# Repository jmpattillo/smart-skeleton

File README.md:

# smart-skeleton

This repository houses all files needed for the Smart Skeleton.  Please see  https://doi.org/10.1152/advan.00145.2019
to learn more about this project.

See update log for latest changes

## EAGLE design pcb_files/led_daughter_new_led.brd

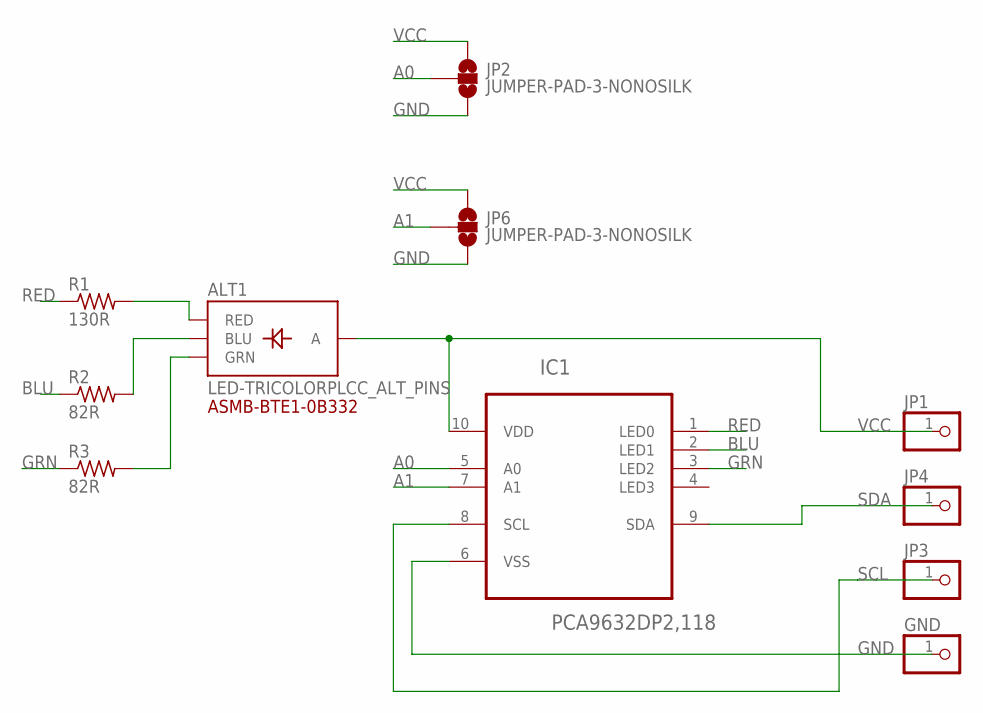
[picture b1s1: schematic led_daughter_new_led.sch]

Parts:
ALT1: LED-TRICOLORPLCC_ALT_PINS; LED-TRICOLOR-PLCC
GND: PINHD-1X1CB; 1X01-CLEANBIG
IC1: PCA9632DP2,118; SOP50P490X110-10N
JP1, JP3, JP4: PINHD-1X1CB; 1X01-CLEANBIG
JP2, JP6: JUMPER-PAD-3-NONOSILK; PAD-JUMPER-3-NO_NO_SILK
R1: 130R; R0603
R2, R3: 82R; R0603

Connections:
A0: IC1.5 (A0), JP2.2
A1: IC1.7 (A1), JP6.2
BLU: IC1.2 (LED1), R2.1
GND: GND.1, IC1.6 (VSS), JP2.3, JP6.3
GRN: IC1.3 (LED2), R3.1
unnamed: ALT1.PAD3 (RED), R1.2
unnamed: ALT1.PAD1 (BLU), R2.2
unnamed: ALT1.PAD4 (GRN), R3.2
RED: IC1.1 (LED0), R1.1
SCL: IC1.8 (SCL), JP3.1
SDA: IC1.9 (SDA), JP4.1
VCC: ALT1.PAD2 (A), IC1.10 (VDD), JP1.1, JP2.1, JP6.1

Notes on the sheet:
ASMB-BTE1-0B332

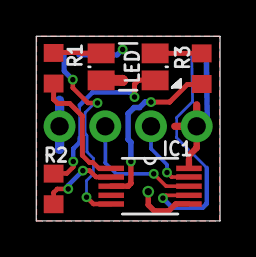
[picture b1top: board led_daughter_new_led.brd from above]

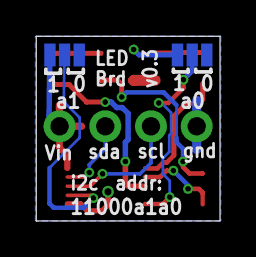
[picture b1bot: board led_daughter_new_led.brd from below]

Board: 2 copper layers, 10.2 x 10.3 mm, 11 parts (2 on the bottom side), 12 nets.

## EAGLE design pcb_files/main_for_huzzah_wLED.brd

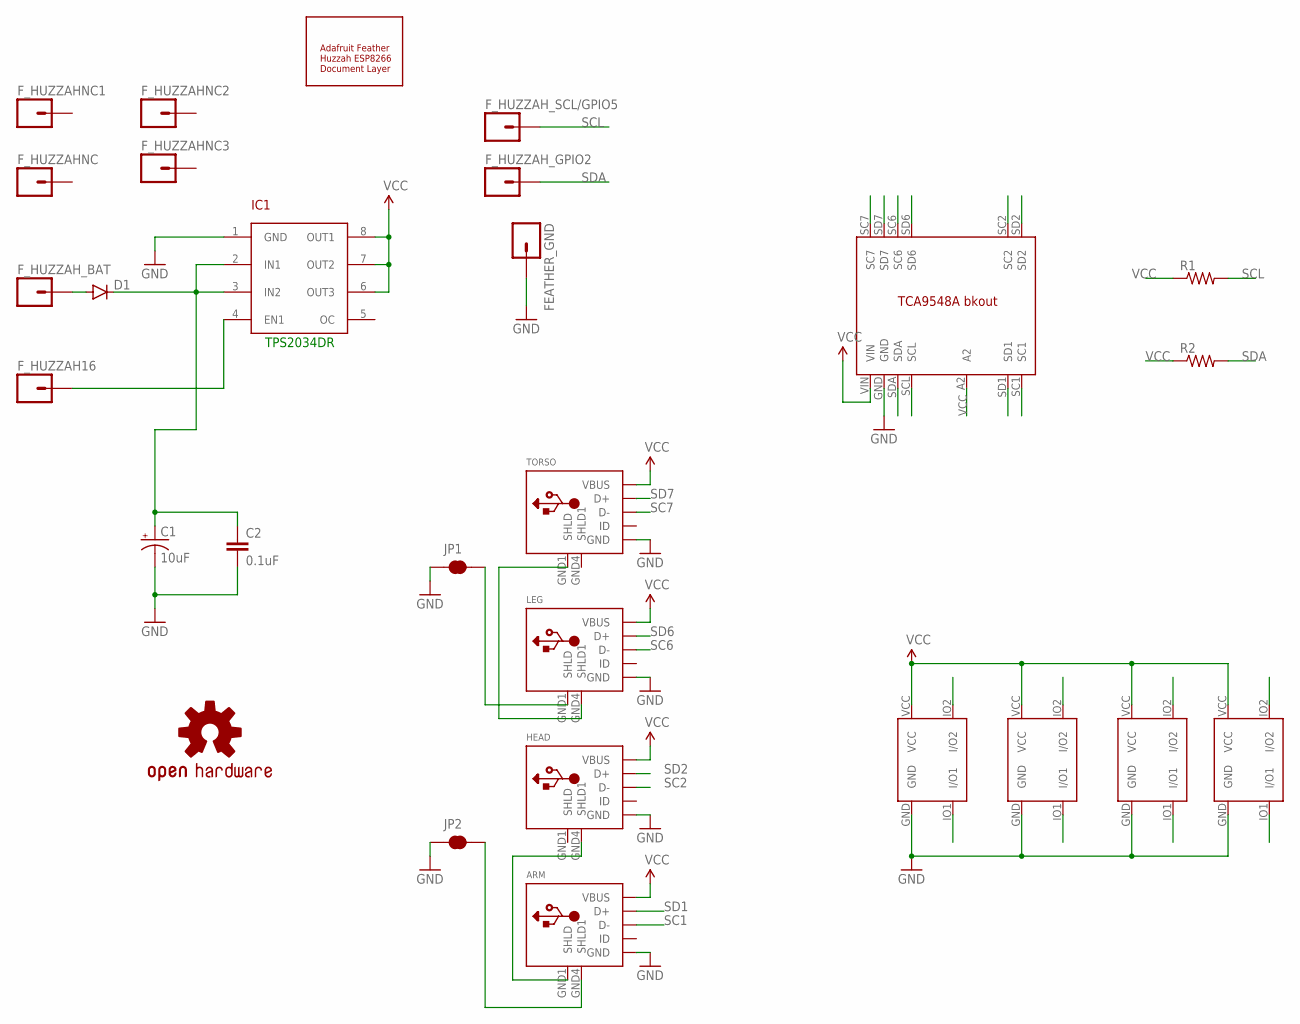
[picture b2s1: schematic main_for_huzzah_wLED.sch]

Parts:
ARM: USB; USB-MINIB-THM-MOLEX_NOSLK
C1: 10uF; CPOL-RADIAL-10UF-25V
C2: 0.1uF; CAP-PTH-SMALL
D1: DIODEKIT2; DIODE-1N4001-KIT
FEATHER_GND: M01; 1X01SMALL_NS
F_HUZZAH16: M01; 1X01SMALL_NS
F_HUZZAHNC, F_HUZZAHNC1, F_HUZZAHNC2, F_HUZZAHNC3: M01; 1X01SMALL_NS
F_HUZZAH_BAT: M01; 1X01SMALL_NS
F_HUZZAH_GPIO2: M01; 1X01SMALL_NS
F_HUZZAH_SCL/GPIO5: M01; 1X01SMALL_NS
HEAD: USB; USB-MINIB-THM-MOLEX_NOSLK
IC1: TPS2055A; SO-08
JP1, JP2: JUMPER-PAD-2-NC_BY_TRACENO_SILK; PAD-JUMPER-2-NC_BY_TRACE_NO_SILK
LEG: USB; USB-MINIB-THM-MOLEX_NOSLK
LOGO1: OSHW-LOGOM; OSHW-LOGO-M
R1, R2: RESISTORAXIAL-0.3; AXIAL-0.3
TORSO: USB; USB-MINIB-THM-MOLEX_NOSLK
U$1: TCA9548_MIN; TCA9548_NOEXTRA
U$2, U$3, U$4, U$5: TVS_ARRAY_CD143A; SOT-143
U$7: FEATHER_HUZZAH_DOCUMENT; FEATHER_HUZZAH_DOC_ONLY

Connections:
GND: ARM.GND, C1.2 (-), C2.2, FEATHER_GND.P$1, HEAD.GND, IC1.1 (GND), JP1.1, JP2.1, LEG.GND, TORSO.GND, U$1.GND, U$2.GND, U$3.GND, U$4.GND, U$5.GND
unnamed: LEG.GND4 (SHLD1), TORSO.GND1 (SHLD)
unnamed: JP1.2, LEG.GND1 (SHLD)
unnamed: ARM.GND1 (SHLD), HEAD.GND4 (SHLD1)
unnamed: ARM.GND4 (SHLD1), JP2.2
unnamed: D1.A, F_HUZZAH_BAT.P$1
unnamed: F_HUZZAH16.P$1, IC1.4 (EN1)
unnamed: C1.1 (+), C2.1, D1.C, IC1.2 (IN1), IC1.3 (IN2)
SC1: ARM.D-, U$1.SC1, U$3.IO1 (I/O1)
SC2: HEAD.D-, U$1.SC2, U$2.IO1 (I/O1)
SC6: LEG.D-, U$1.SC6, U$5.IO1 (I/O1)
SC7: TORSO.D-, U$1.SC7, U$4.IO1 (I/O1)
SCL: F_HUZZAH_SCL/GPIO5.P$1, R1.P$2 (2), U$1.SCL
SD1: ARM.D+, U$1.SD1, U$3.IO2 (I/O2)
SD2: HEAD.D+, U$1.SD2, U$2.IO2 (I/O2)
SD6: LEG.D+, U$1.SD6, U$5.IO2 (I/O2)
SD7: TORSO.D+, U$1.SD7, U$4.IO2 (I/O2)
SDA: F_HUZZAH_GPIO2.P$1, R2.P$2 (2), U$1.SDA
VCC: ARM.VBUS, HEAD.VBUS, IC1.6 (OUT3), IC1.7 (OUT2), IC1.8 (OUT1), LEG.VBUS, R1.P$1 (1), R2.P$1 (1), TORSO.VBUS, U$1.A2, U$1.VIN, U$2.VCC, U$3.VCC, U$4.VCC, U$5.VCC

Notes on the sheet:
TPS2034DR

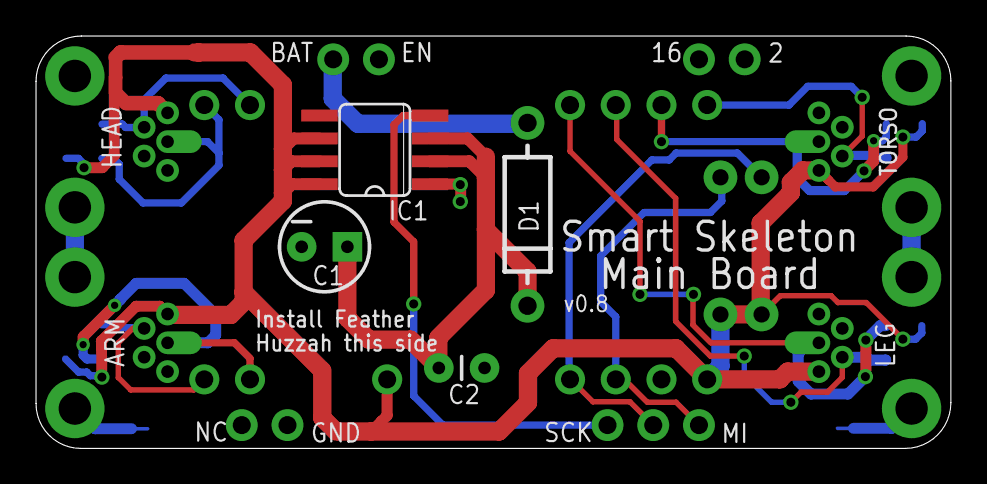
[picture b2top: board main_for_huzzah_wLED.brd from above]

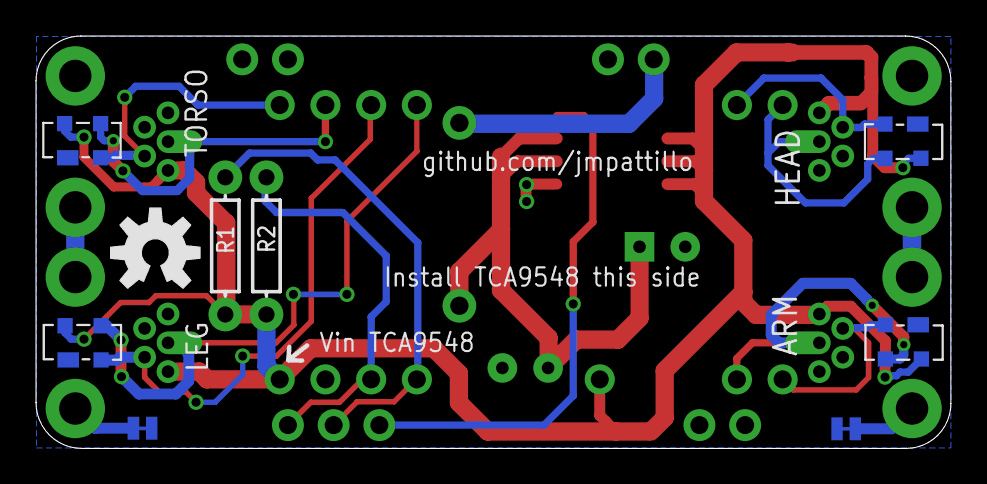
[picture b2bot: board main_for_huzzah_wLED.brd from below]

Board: 2 copper layers, 50.8 x 22.9 mm, 28 parts (10 on the bottom side), 19 nets.

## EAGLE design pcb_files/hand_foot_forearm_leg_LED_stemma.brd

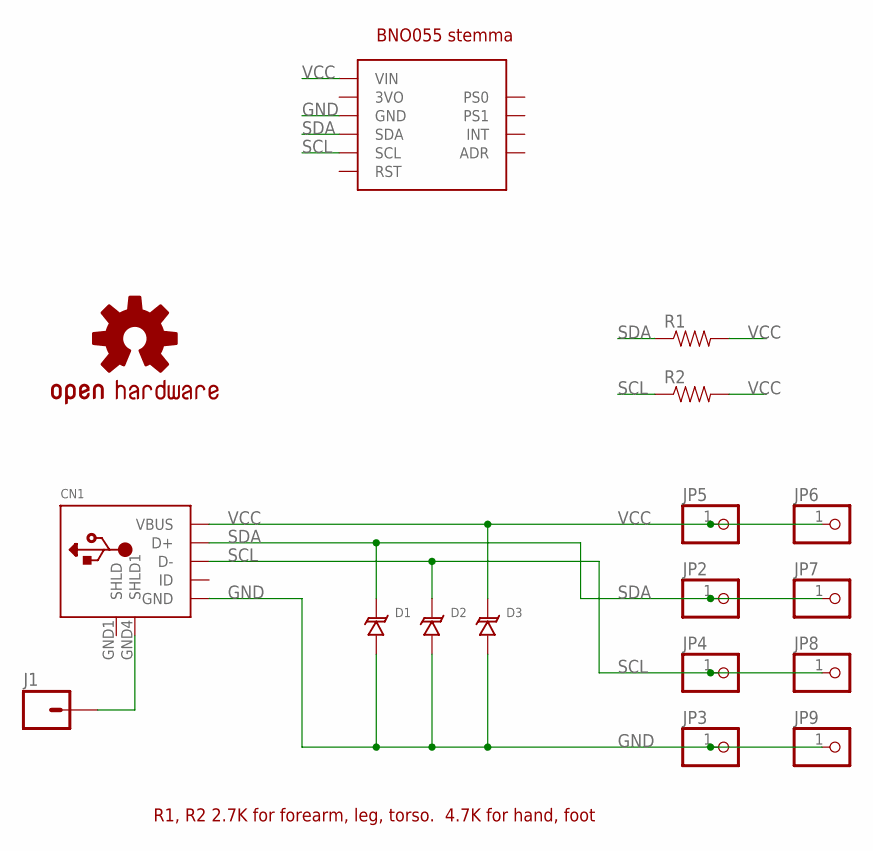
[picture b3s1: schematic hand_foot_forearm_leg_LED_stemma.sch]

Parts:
CN1: USB; USB-MINIB-THM-MOLEX_NOSLK
D1, D2, D3: TVS_DIODE_SOD723; SOD723
J1: M01PTH; 1X01
JP2, JP3, JP4, JP5, JP6, JP7, JP8, JP9: PINHD-1X1CB; 1X01-CLEANBIG
LOGO1: OSHW-LOGOS; OSHW-LOGO-S
R1, R2: RESISTORAXIAL-0.3; AXIAL-0.3
U$2: BNO_055_STEMMA; BNO_STEMMA

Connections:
GND: CN1.GND, D1.A, D2.A, D3.A, JP3.1, JP9.1, U$2.GND
SCL: CN1.D-, D2.C, JP4.1, JP8.1, R2.P$1 (1), U$2.SCL
SDA: CN1.D+, D1.C, JP2.1, JP7.1, R1.P$1 (1), U$2.SDA
SHIELD: CN1.GND4 (SHLD1), J1.1
VCC: CN1.VBUS, D3.C, JP5.1, JP6.1, R1.P$2 (2), R2.P$2 (2), U$2.VIN

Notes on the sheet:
R1, R2 2.7K for forearm, leg, torso. 4.7K for hand, foot
BNO055 stemma

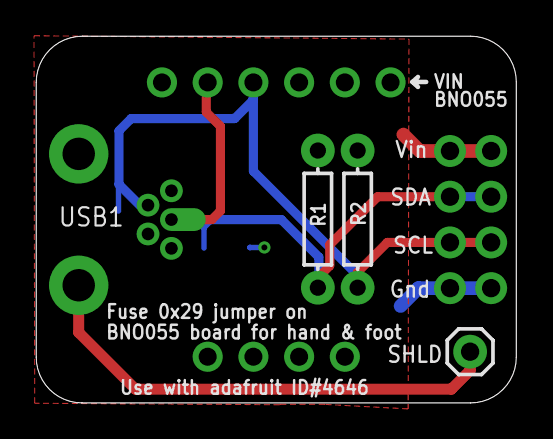
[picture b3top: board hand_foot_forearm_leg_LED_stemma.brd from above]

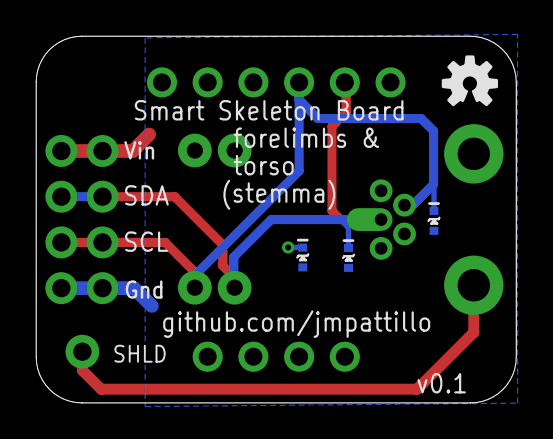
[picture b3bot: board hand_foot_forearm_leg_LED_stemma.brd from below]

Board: 2 copper layers, 26.7 x 20.4 mm, 17 parts (4 on the bottom side), 5 nets.

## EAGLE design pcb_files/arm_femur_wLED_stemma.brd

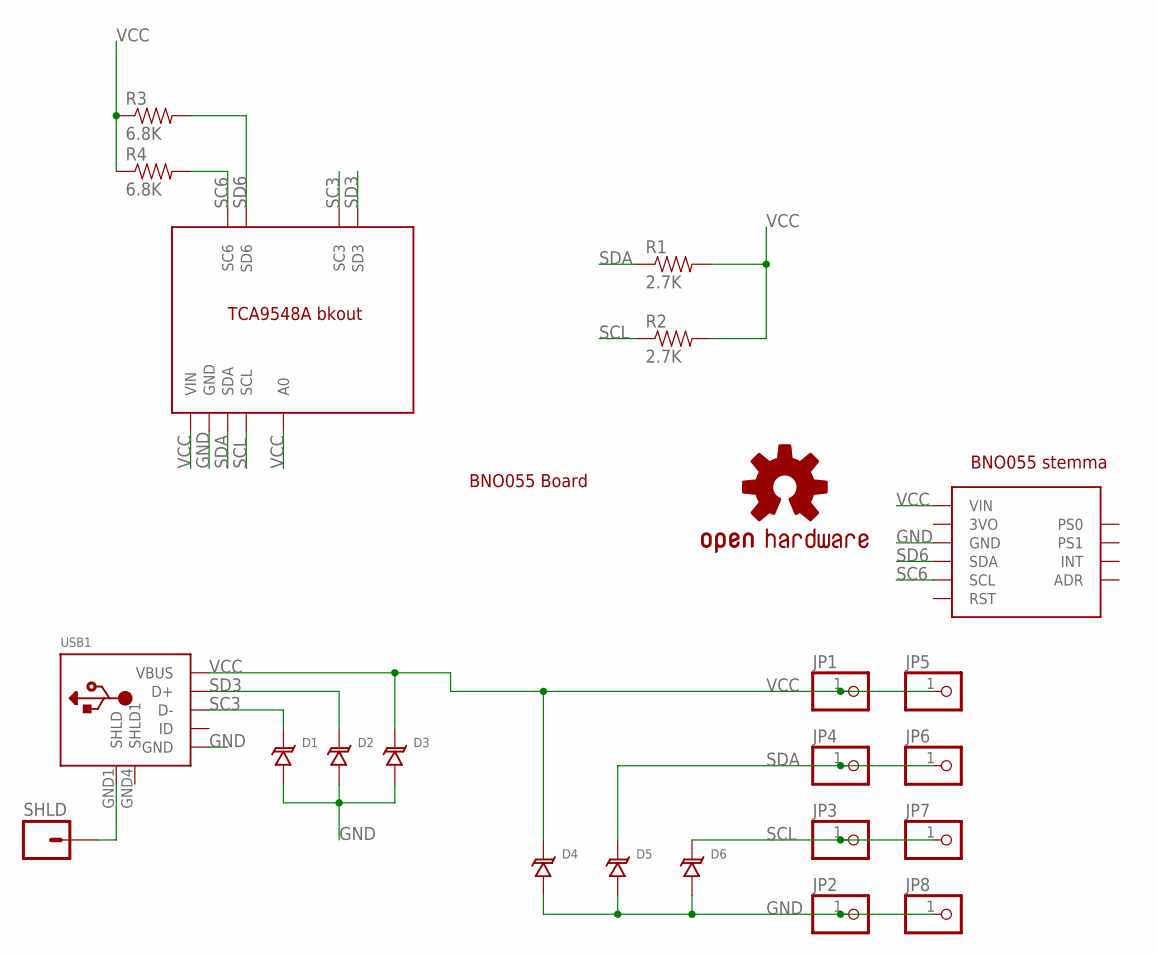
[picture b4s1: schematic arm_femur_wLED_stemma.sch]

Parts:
D1, D2, D3, D4, D5, D6: TVS_DIODE_SOD723; SOD723
JP1, JP2, JP3, JP4, JP5, JP6, JP7, JP8: PINHD-1X1CB; 1X01-CLEANBIG
LOGO1: OSHW-LOGOM; OSHW-LOGO-M
R1, R2: 2.7K; AXIAL-0.3
R3, R4: 6.8K; AXIAL-0.3
SHLD: M01PTH; 1X01
U$2: TCA9548_ARM_FEMUR
U$3: BNO_055_STEMMA; BNO_STEMMA
USB1: USB; USB-MINIB-THM-MOLEX_NOSLK

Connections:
GND: D1.A, D2.A, D3.A, D4.A, D5.A, D6.A, JP2.1, JP8.1, U$2.GND, U$3.GND, USB1.GND
unnamed: SHLD.1, USB1.GND1 (SHLD)
SC3: D1.C, U$2.SC3, USB1.D-
SC6: R4.P$2 (2), U$2.SC6, U$3.SCL
SCL: D6.C, JP3.1, JP7.1, R2.P$1 (1), U$2.SCL
SD3: D2.C, U$2.SD3, USB1.D+
SD6: R3.P$2 (2), U$2.SD6, U$3.SDA
SDA: D5.C, JP4.1, JP6.1, R1.P$1 (1), U$2.SDA
VCC: D3.C, D4.C, JP1.1, JP5.1, R1.P$2 (2), R2.P$2 (2), R3.P$1 (1), R4.P$1 (1), U$2.A0, U$2.VIN, U$3.VIN, USB1.VBUS

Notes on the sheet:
BNO055 Board
BNO055 stemma

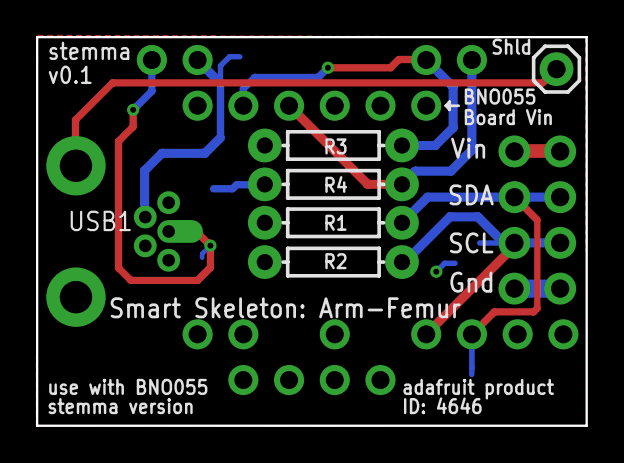
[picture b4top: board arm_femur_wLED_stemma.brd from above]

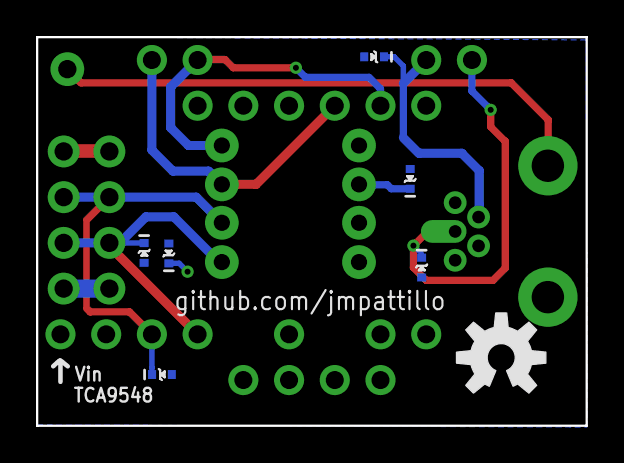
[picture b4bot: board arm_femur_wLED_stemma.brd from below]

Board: 2 copper layers, 30.5 x 21.6 mm, 23 parts (8 on the bottom side), 9 nets.

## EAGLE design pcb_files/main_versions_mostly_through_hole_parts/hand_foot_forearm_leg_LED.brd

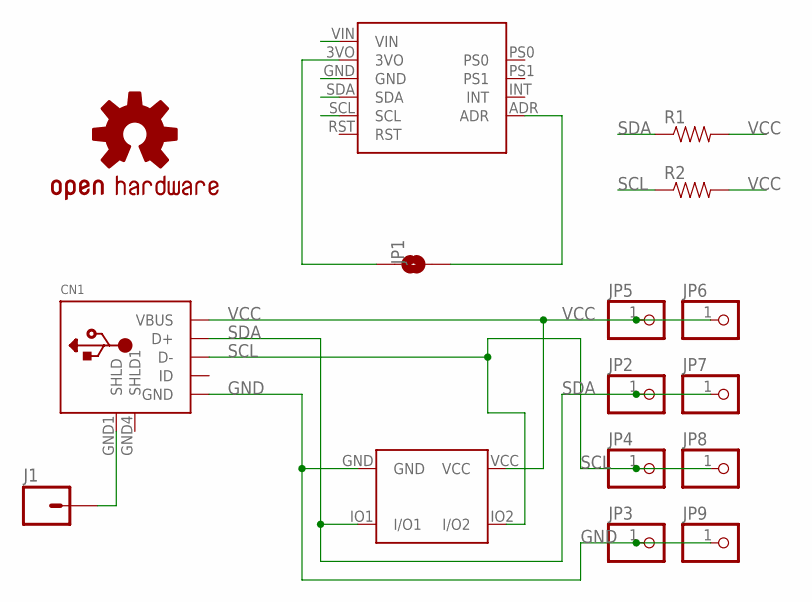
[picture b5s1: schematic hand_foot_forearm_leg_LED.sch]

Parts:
CN1: USB; USB-MINIB-THM-MOLEX_NOSLK
J1: M01PTH; 1X01
JP1: JUMPER-PAD-2-NO; PAD-JUMPER-2-NO_NO_SILK
JP2, JP3, JP4, JP5, JP6, JP7, JP8, JP9: PINHD-1X1CB; 1X01-CLEANBIG
LOGO1: OSHW-LOGOS; OSHW-LOGO-S
R1, R2: RESISTORAXIAL-0.3; AXIAL-0.3
U$1: BNO_055_BKOUT; BNO_BKOUT
U$2: TVS_ARRAY_CD143A; SOT-143

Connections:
GND: CN1.GND, JP3.1, JP9.1, U$1.GND, U$2.GND
unnamed: JP1.1, U$1.3VO
unnamed: JP1.2, U$1.ADR
SCL: CN1.D-, JP4.1, JP8.1, R2.P$1 (1), U$1.SCL, U$2.IO2 (I/O2)
SDA: CN1.D+, JP2.1, JP7.1, R1.P$1 (1), U$1.SDA, U$2.IO1 (I/O1)
SHIELD: CN1.GND1 (SHLD), J1.1
VCC: CN1.VBUS, JP5.1, JP6.1, R1.P$2 (2), R2.P$2 (2), U$1.VIN, U$2.VCC

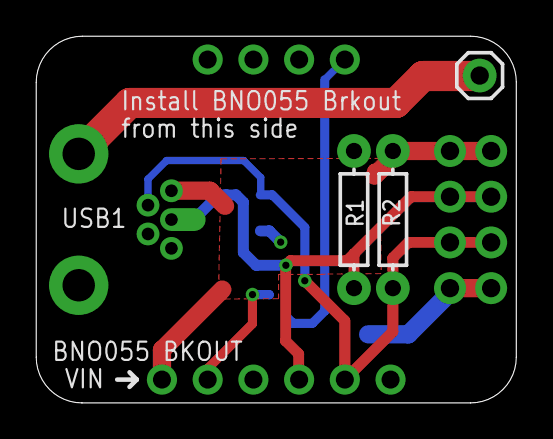
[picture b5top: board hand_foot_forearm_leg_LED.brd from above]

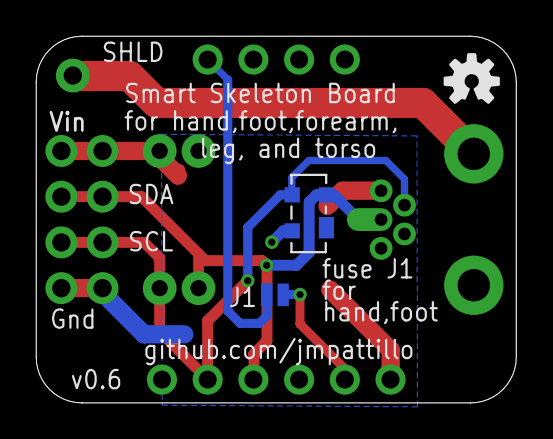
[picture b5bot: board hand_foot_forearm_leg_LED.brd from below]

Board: 2 copper layers, 26.7 x 20.4 mm, 16 parts (3 on the bottom side), 7 nets.

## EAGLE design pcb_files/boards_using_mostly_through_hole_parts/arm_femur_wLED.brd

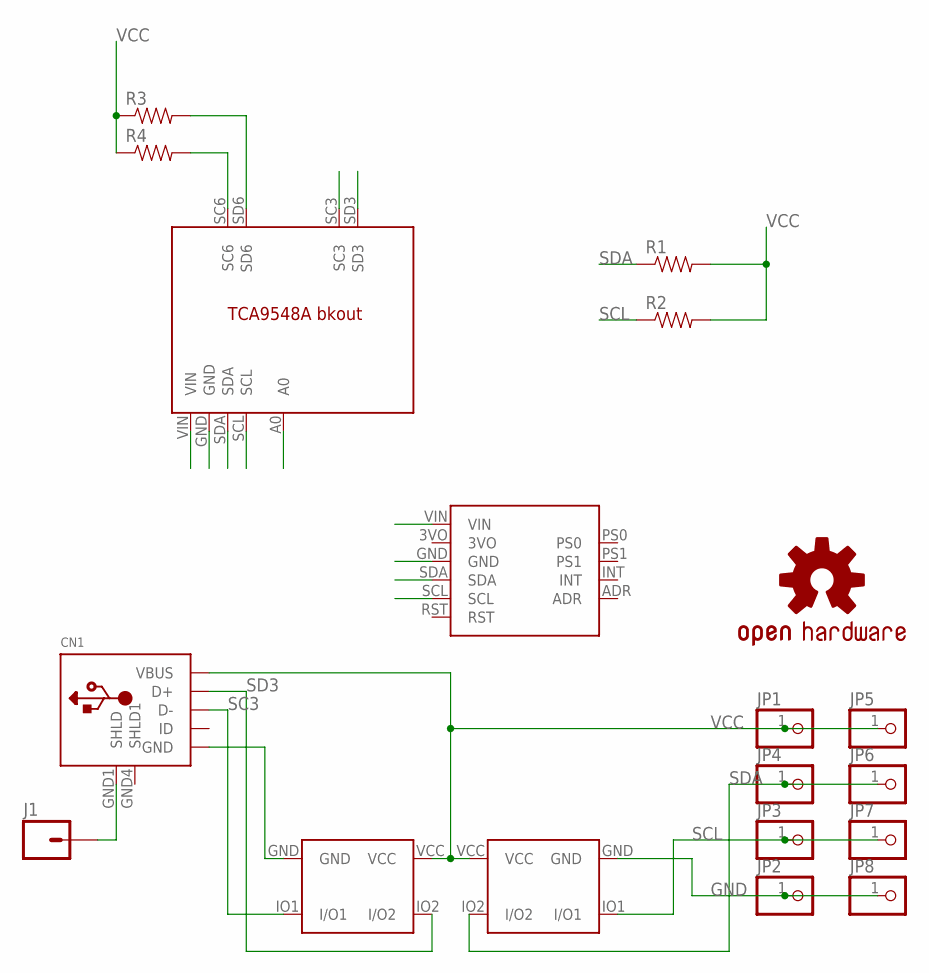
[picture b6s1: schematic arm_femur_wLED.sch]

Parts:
CN1: USB; USB-MINIB-THM-MOLEX_NOSLK
J1: M01PTH; 1X01
JP1, JP2, JP3, JP4, JP5, JP6, JP7, JP8: PINHD-1X1CB; 1X01-CLEANBIG
LOGO1: OSHW-LOGOM; OSHW-LOGO-M
R1, R2, R3, R4: RESISTORAXIAL-0.3; AXIAL-0.3
U$1: BNO_055_BKOUT; BNO_BKOUT
U$2: TCA9548_ARM_FEMUR
U$3, U$4: TVS_ARRAY_CD143A; SOT-143

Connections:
GND: CN1.GND, JP2.1, JP8.1, U$1.GND, U$2.GND, U$3.GND, U$4.GND
unnamed: CN1.GND1 (SHLD), J1.1
SC3: CN1.D-, U$2.SC3, U$4.IO1 (I/O1)
SC6: R4.P$2 (2), U$1.SCL, U$2.SC6
SCL: JP3.1, JP7.1, R2.P$1 (1), U$2.SCL, U$3.IO1 (I/O1)
SD3: CN1.D+, U$2.SD3, U$4.IO2 (I/O2)
SD6: R3.P$2 (2), U$1.SDA, U$2.SD6
SDA: JP4.1, JP6.1, R1.P$1 (1), U$2.SDA, U$3.IO2 (I/O2)
VCC: CN1.VBUS, JP1.1, JP5.1, R1.P$2 (2), R2.P$2 (2), R3.P$1 (1), R4.P$1 (1), U$1.VIN, U$2.A0, U$2.VIN, U$3.VCC, U$4.VCC

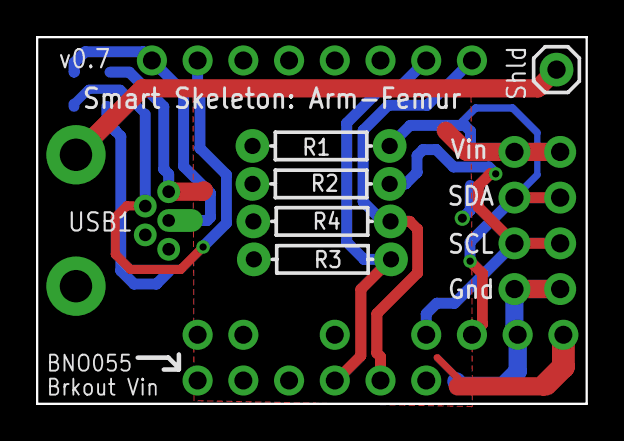
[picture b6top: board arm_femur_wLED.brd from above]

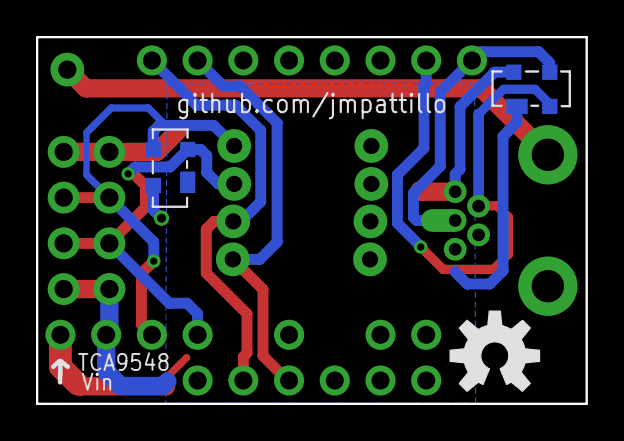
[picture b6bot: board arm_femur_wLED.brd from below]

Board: 2 copper layers, 30.5 x 20.4 mm, 19 parts (4 on the bottom side), 9 nets.

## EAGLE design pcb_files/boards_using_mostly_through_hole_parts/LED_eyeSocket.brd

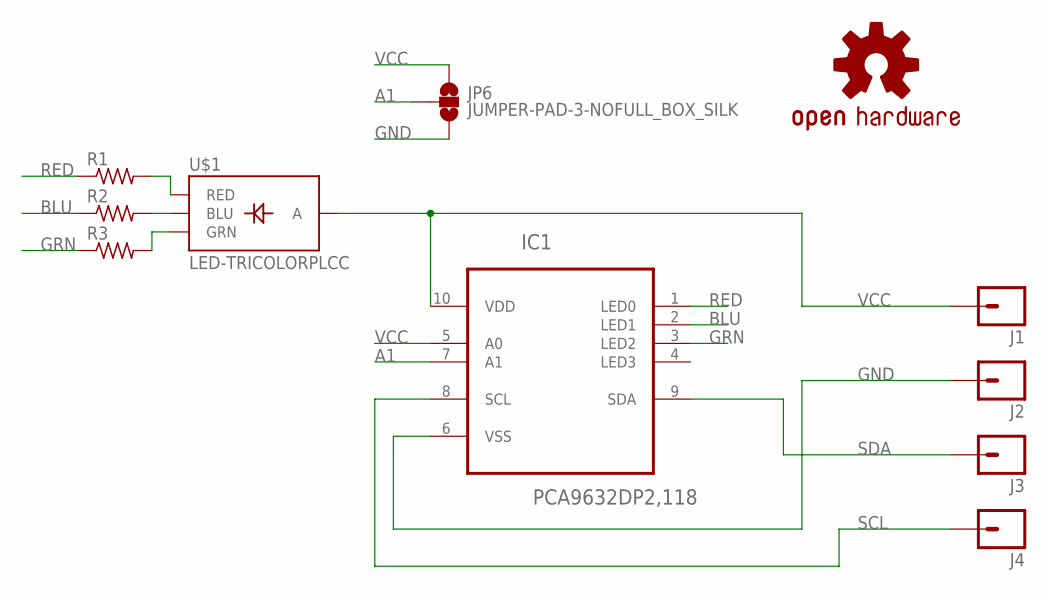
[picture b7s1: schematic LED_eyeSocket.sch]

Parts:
IC1: PCA9632DP2,118; SOP50P490X110-10N
J1, J2, J3, J4: M01NOSILK-KIT; 1X01NS-KIT
JP6: JUMPER-PAD-3-NOFULL_BOX_SILK; PAD-JUMPER-3-NO_YES_SILK_FULL_BOX
LOGO1: OSHW-LOGOS; OSHW-LOGO-S
R1, R2, R3: R-US_R0603; R0603
U$1: LED-TRICOLORPLCC; LED-TRICOLOR-PLCC

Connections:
A1: IC1.7 (A1), JP6.2
BLU: IC1.2 (LED1), R2.1
GND: IC1.6 (VSS), J2.1, JP6.3
GRN: IC1.3 (LED2), R3.1
unnamed: R1.2, U$1.PAD4 (RED)
unnamed: R2.2, U$1.PAD2 (BLU)
unnamed: R3.2, U$1.PAD3 (GRN)
RED: IC1.1 (LED0), R1.1
SCL: IC1.8 (SCL), J4.1
SDA: IC1.9 (SDA), J3.1
VCC: IC1.5 (A0), IC1.10 (VDD), J1.1, JP6.1, U$1.PAD1 (A)

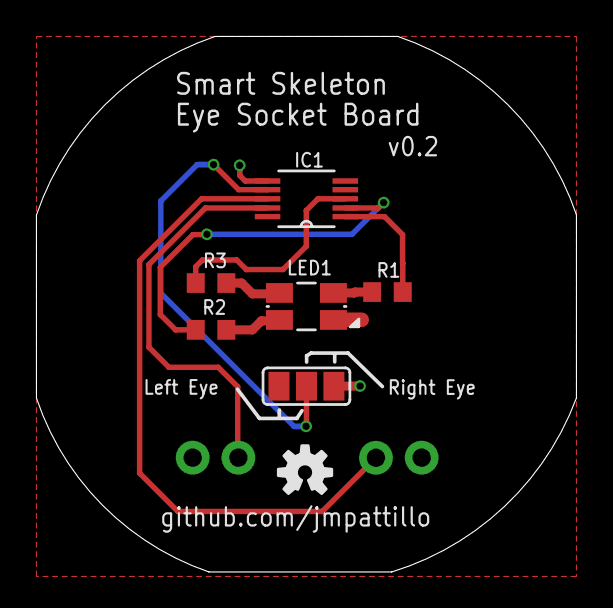
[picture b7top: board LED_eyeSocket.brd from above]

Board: 2 copper layers, 30.0 x 29.8 mm, 11 parts (0 on the bottom side), 11 nets.

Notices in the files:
parts and their libraries:
SparkFun-Connectors: Licensing: Creative Commons ShareAlike 4.0 International - https://creativecommons.org/licenses/by-sa/4.0
